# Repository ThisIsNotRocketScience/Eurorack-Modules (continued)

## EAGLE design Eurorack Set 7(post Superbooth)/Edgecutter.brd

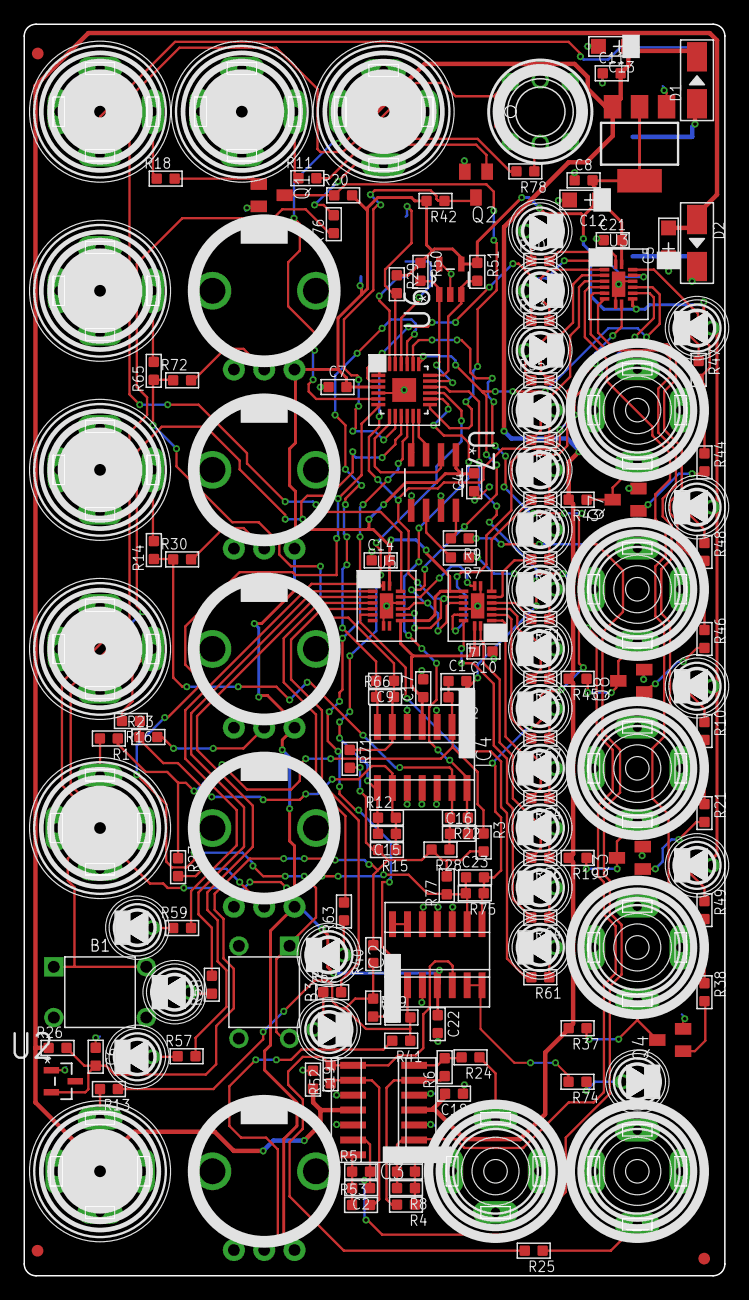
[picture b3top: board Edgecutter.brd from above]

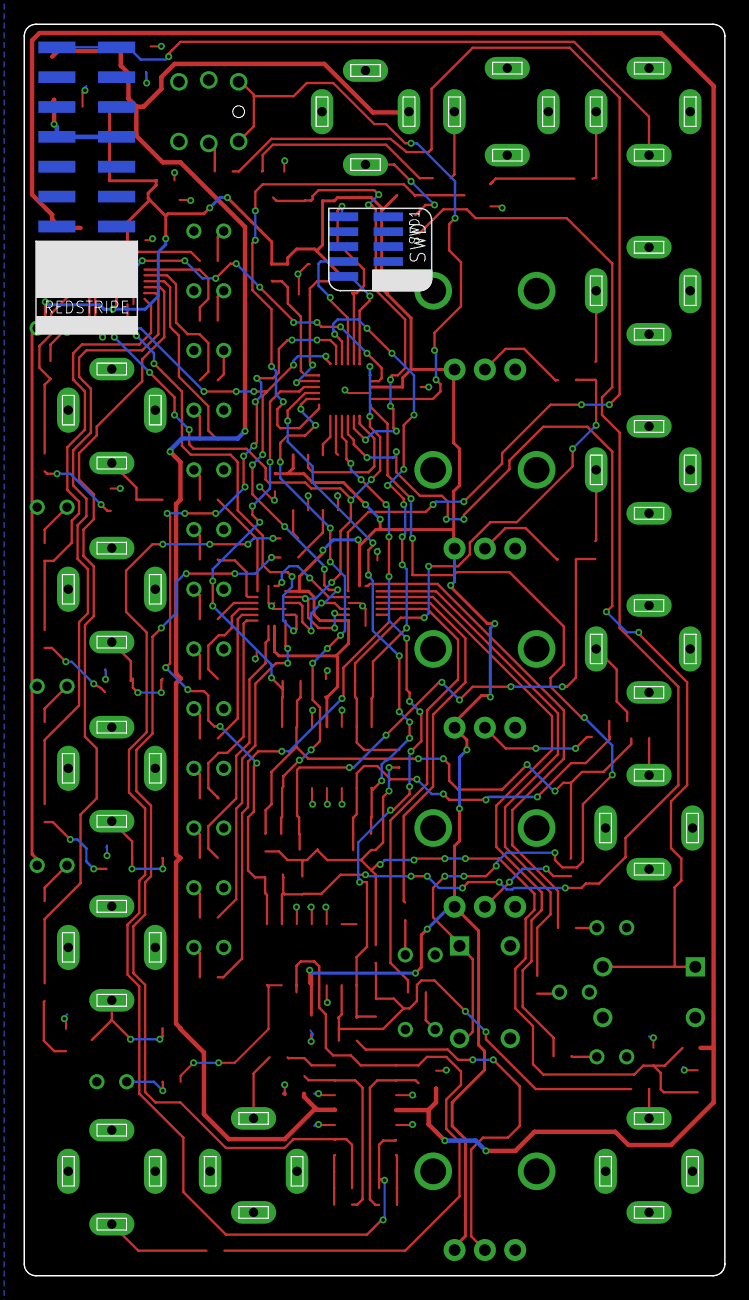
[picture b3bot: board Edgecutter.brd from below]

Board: 2 copper layers, 59.6 x 106.5 mm, 166 parts (2 on the bottom side), 122 nets.

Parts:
B1, B3: BUTTON-4P-3110040P1; 4P-6.0X6.0X5.0H
C1, C2, C3, C9, C15, C16, C20, C23: 3.3nF; C0603
C4, C6, C7, C8, C10, C11, C14, C17, C18, C19, C21, C22: 100nF; C0603
C5, C12, C13: 10uF; AVX-A
D1, D2: MRA4004T3G; DO-214AC
D3, D4, D5, D24, D25, D26, D27, D28, D29, D30, D31, D32, D33, D34, D35, D36, D37, D38, D39, D40, D41, D43, D44: yellow; 3MMLED
FID1, FID2, FID3: FIDUCIAL; FIDUCIAL_1MM
IC1: LD1117AS33TR; SOT223
IC2, IC4: MCP6004; SO14
IC3: TL074D; SO14
J1, J2, J3, J4, J5, J6, J9, J15: PJ-341; 3.5MM-JACK-SWITCH-13MM-INPUT
J7, J8, J10, J11, J12, J13: PJ-341; 3.5MM-JACK-SWITCH-13MM-OUTPUT
J14: POWERSMT; 2X08_SMT_HEADER
OUTLINE: EURORACK_PCB12HP; EURORACK12HPPCB
Q1, Q2, Q3, Q4, Q7, Q8: MMBT3904; SOT23-BEC
R1, R4, R6, R11, R13, R14, R16, R18, R21, R38, R44, R46, R52, R53, R65, R76: 100k; R0603
R2, R12, R22, R23, R27, R30, R39, R41, R66, R72, R75: 33k; R0603
R3, R15, R28, R40, R71, R77: 51k; R0603
R5, R8: 30k; R0603
R7, R9: 12k; R0603
R10, R31, R32, R33, R34, R35, R36, R47, R48, R49, R54, R55, R56, R57, R58, R59, R60, R61, R62, R63, R64, R67, R74, R78: 56; R0603
R17, R68, R69, R70, R73: 10kB; OG-POTS_ALPS_POT_VERTICAL
R19, R20, R26, R29, R37, R42, R43, R45: 10k; R0603
R24, R25: 100; R0603
R50, R51: 2k; R0603
SWD1: CORTEX_SWD; M50-3600542
U1: MKL02Z32VFK4; QFN50P400X400X100-25N
U2: LM4040DIM3-5.0; SOT95P237X112-3N
U3, U4, U5: 74HC595BQ; QFN50P250X350X100-17N
U6: 24LC16T-I/OT; SOT95P290X145-5N
U7: MCP4822-E/SN; SOIC8-N_MC
U$2: SWITCH_W_LED_PB6149L-X-102YELLOW; PB6149L

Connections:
3.3V: C4.2, C7.2, C8.2, C10.2, C12.+, C14.2, C17.1, C21.2, C22.1, D40.+, D41.+, D43.+, D44.+, IC1.2, IC1.4, IC2.4, IC4.4, R17.P$3, R20.2, R29.1, R42.2, R50.1, R51.1, R68.P$3, R69.P$3, R70.P$3, R73.P$3, SWD1.1, U1.3, U3.10, U3.16, U4.10, U4.16, U5.10, U5.16, U6.4, U7.1
12V: C11.2, C13.+, C18.2, D1.2, IC1.3, IC3.4, J9.SWITCH@3, R19.2, R37.2, R43.2, R45.2
-12V: C5.-, C19.2, D2.1, IC3.11, R26.1
ADC_ATTACK: C9.2, IC4.7, R66.1, U1.21
ADC_CURVE: C20.2, IC2.1, R39.1, U1.10
ADC_DECAY: C16.2, IC4.14, R22.1, U1.14
ADC_RELEASE: C1.2, IC4.1, R2.1, U1.16
ADC_SUSTAIN: C15.2, IC4.8, R12.1, U1.15
ADC_VELOCITY: C23.2, IC2.8, R75.1, U1.20
BUTTON_LOOP: B3.1, B3.4, U1.6
BUTTON_TIMERANGE: B1.1, B1.4, U1.9
BUTTON_TRIGGER: U1.5, U$2.1, U$2.2
CLOCK: U1.1, U3.11, U4.11, U5.11
CPU_RESET: R29.2, SWD1.10, U1.23
D21: D43.-, R47.1
DACCS: U1.7, U7.2
DACSCK: U1.12, U7.3
DACSDI: U1.11, U7.4
EXTGATE: J5.SWITCH@3, J14.15, J14.16
GND: B1.2, B1.3, B3.2, B3.3, C4.1, C5.+, C6.1, C7.1, C8.1, C10.1, C11.1, C12.-, C13.-, C14.1, C17.2, C18.1, C19.1, C21.1, C22.2, D3.-, D4.-, D5.-, D24.-, D25.-, D26.-, D27.-, D28.-, D29.-, D30.-, D31.-, D32.-, D33.-, D34.-, D35.-, D36.-, D37.-, D38.-, D39.-, IC1.1, IC2.3, IC2.10, IC2.11, IC2.12, IC3.3, IC3.5, IC3.10, IC3.12, IC4.3, IC4.5, IC4.10, IC4.11, IC4.12, J1.RING@3, J1.SWITCH@3, J2.RING@3, J2.SWITCH@3, J3.RING@3, J3.SWITCH@3, J4.RING@3, J4.SWITCH@3, J5.RING@3, J6.RING@3, J6.SWITCH@3, J7.RING@3, J8.RING@3, J9.RING@3, J10.RING@3, J11.RING@3, J12.RING@3, J13.RING@3, J14.3, J14.4, J14.5, J14.6, J14.7, J14.8, J15.RING@3, J15.SWITCH@3, Q1.E, Q2.E, Q3.E, Q4.E, Q7.E, Q8.E, R17.P$1, R68.P$1, R69.P$1, R70.P$1, R73.P$1, SWD1.3, SWD1.5, U1.4, U1.25, U2.1, U3.8, U3.13, U3.17, U4.8, U4.13, U4.17, U5.8, U5.13, U5.17, U6.2, U6.5, U7.5, U7.7, U$2.3, U$2.4, U$2.LEDNEG
KNOB_ATTACK: R72.2, R73.P$2
KNOB_CURVE: R41.2, R70.P$2
KNOB_DECAY: R17.P$2, R30.2
KNOB_RELEASE: R27.2, R69.P$2
KNOB_SUSTAIN: R23.2, R68.P$2
LATCH: U1.19, U3.12, U4.12, U5.12
unnamed: R78.1, U$2.LEDPOS
unnamed: IC3.6, R4.2, R6.1
unnamed: J2.TIP@3, R16.2
unnamed: C15.1, IC4.9, R12.2, R15.1, R16.1, R23.1
unnamed: R9.2, U7.8
unnamed: J3.TIP@3, R1.2
unnamed: R7.2, U7.6
unnamed: C1.1, IC4.2, R1.1, R2.2, R3.1, R27.1
unnamed: C2.1, IC3.13, R5.2, R9.1
unnamed: C3.1, IC3.2, R7.1, R8.2
unnamed: J15.TIP@3, R65.2
unnamed: J4.TIP@3, R13.2
unnamed: D1.1, J14.9, J14.10
unnamed: R34.2, U4.7
unnamed: Q1.B, R18.2
unnamed: J5.TIP@3, R18.1
unnamed: IC3.9, R52.1, R53.2
unnamed: C3.2, IC3.1, R4.1, R8.1
unnamed: IC2.6, IC2.7, R74.2
unnamed: J13.TIP@3, R25.1
unnamed: J12.TIP@3, R24.1
unnamed: C9.1, IC4.6, R65.1, R66.2, R71.1, R72.1
unnamed: D40.-, R10.1
unnamed: C2.2, IC3.14, R5.1, R53.1
unnamed: Q3.B, R21.2
unnamed: IC2.13, IC2.14
unnamed: R64.2, U4.15
unnamed: D28.+, R62.1
unnamed: J7.TIP@3, Q3.C, R19.1
unnamed: D4.+, R67.1
unnamed: R60.2, U3.1
unnamed: D29.+, R61.1
unnamed: J1.TIP@3, R14.2
unnamed: C16.1, IC4.13, R14.1, R22.2, R28.1, R30.1
unnamed: R33.2, U3.2
unnamed: R55.2, U3.3
unnamed: R35.2, U3.4
unnamed: R56.2, U4.1
unnamed: R54.2, U4.2
unnamed: R67.2, U4.3
unnamed: R32.2, U4.4
unnamed: R31.2, U4.5
unnamed: Q2.B, R11.2
unnamed: D41.-, R49.1
unnamed: D44.-, R48.1
unnamed: C20.1, IC2.2, R13.1, R39.2, R40.1, R41.1
unnamed: J6.TIP@3, R11.1
unnamed: R36.2, U4.6
unnamed: R59.2, U5.1
unnamed: R58.2, U5.2
unnamed: D3.+, R60.1
unnamed: R57.2, U5.3
unnamed: R63.2, U5.4
unnamed: R62.2, U5.5
unnamed: R61.2, U5.6
unnamed: C23.1, IC2.9, R75.2, R76.1, R77.1
unnamed: Q4.B, R38.2
unnamed: J8.TIP@3, Q4.C, R37.1
unnamed: D5.+, R74.1
unnamed: J9.TIP@3, R76.2
unnamed: D2.2, J14.1, J14.2
unnamed: Q7.B, R44.2
unnamed: J10.TIP@3, Q7.C, R43.1
unnamed: Q8.B, R46.2
unnamed: J11.TIP@3, Q8.C, R45.1
unnamed: D27.+, R57.1
unnamed: D26.+, R56.1
unnamed: D25.+, R58.1
unnamed: D24.+, R59.1
unnamed: D30.+, R63.1
unnamed: D31.+, R64.1
unnamed: D32.+, R33.1
unnamed: D33.+, R32.1
unnamed: D34.+, R31.1
unnamed: D35.+, R34.1
unnamed: D36.+, R55.1
unnamed: D37.+, R54.1
unnamed: D38.+, R35.1
unnamed: D39.+, R36.1
OUT_ATTACK: R44.1, R47.2, U3.15
OUT_CUR_PRERES: IC2.5, IC3.8, R25.2, R52.2
OUT_DECAY: R46.1, R48.2, U3.7
OUT_LIN_PRERES: IC3.7, R6.2, R24.2
OUT_RELEASEDONE: R38.1, R49.2, U3.5
OUT_RELEASESTART: R10.2, R21.1, U3.6
REF_-5V: C6.2, R3.2, R15.2, R26.2, R28.2, R40.2, R71.2, R77.2, U2.2
RETRIGGER_ENVELOPE: Q2.C, R42.1, U1.8
SCL: R50.2, U1.17, U6.1
SDA: R51.2, U1.18, U6.3
SHIFTER1TO2: U3.9, U4.14
SHIFTER2TO3: U4.9, U5.14
SHIFTERS: U1.2, U3.14
SWD_CLK: SWD1.4, U1.22
SWD_DIO: SWD1.2, U1.24
TRIGGER_ENVELOPE: Q1.C, R20.1, U1.13
TRIGGER_LED: R78.2, U5.15

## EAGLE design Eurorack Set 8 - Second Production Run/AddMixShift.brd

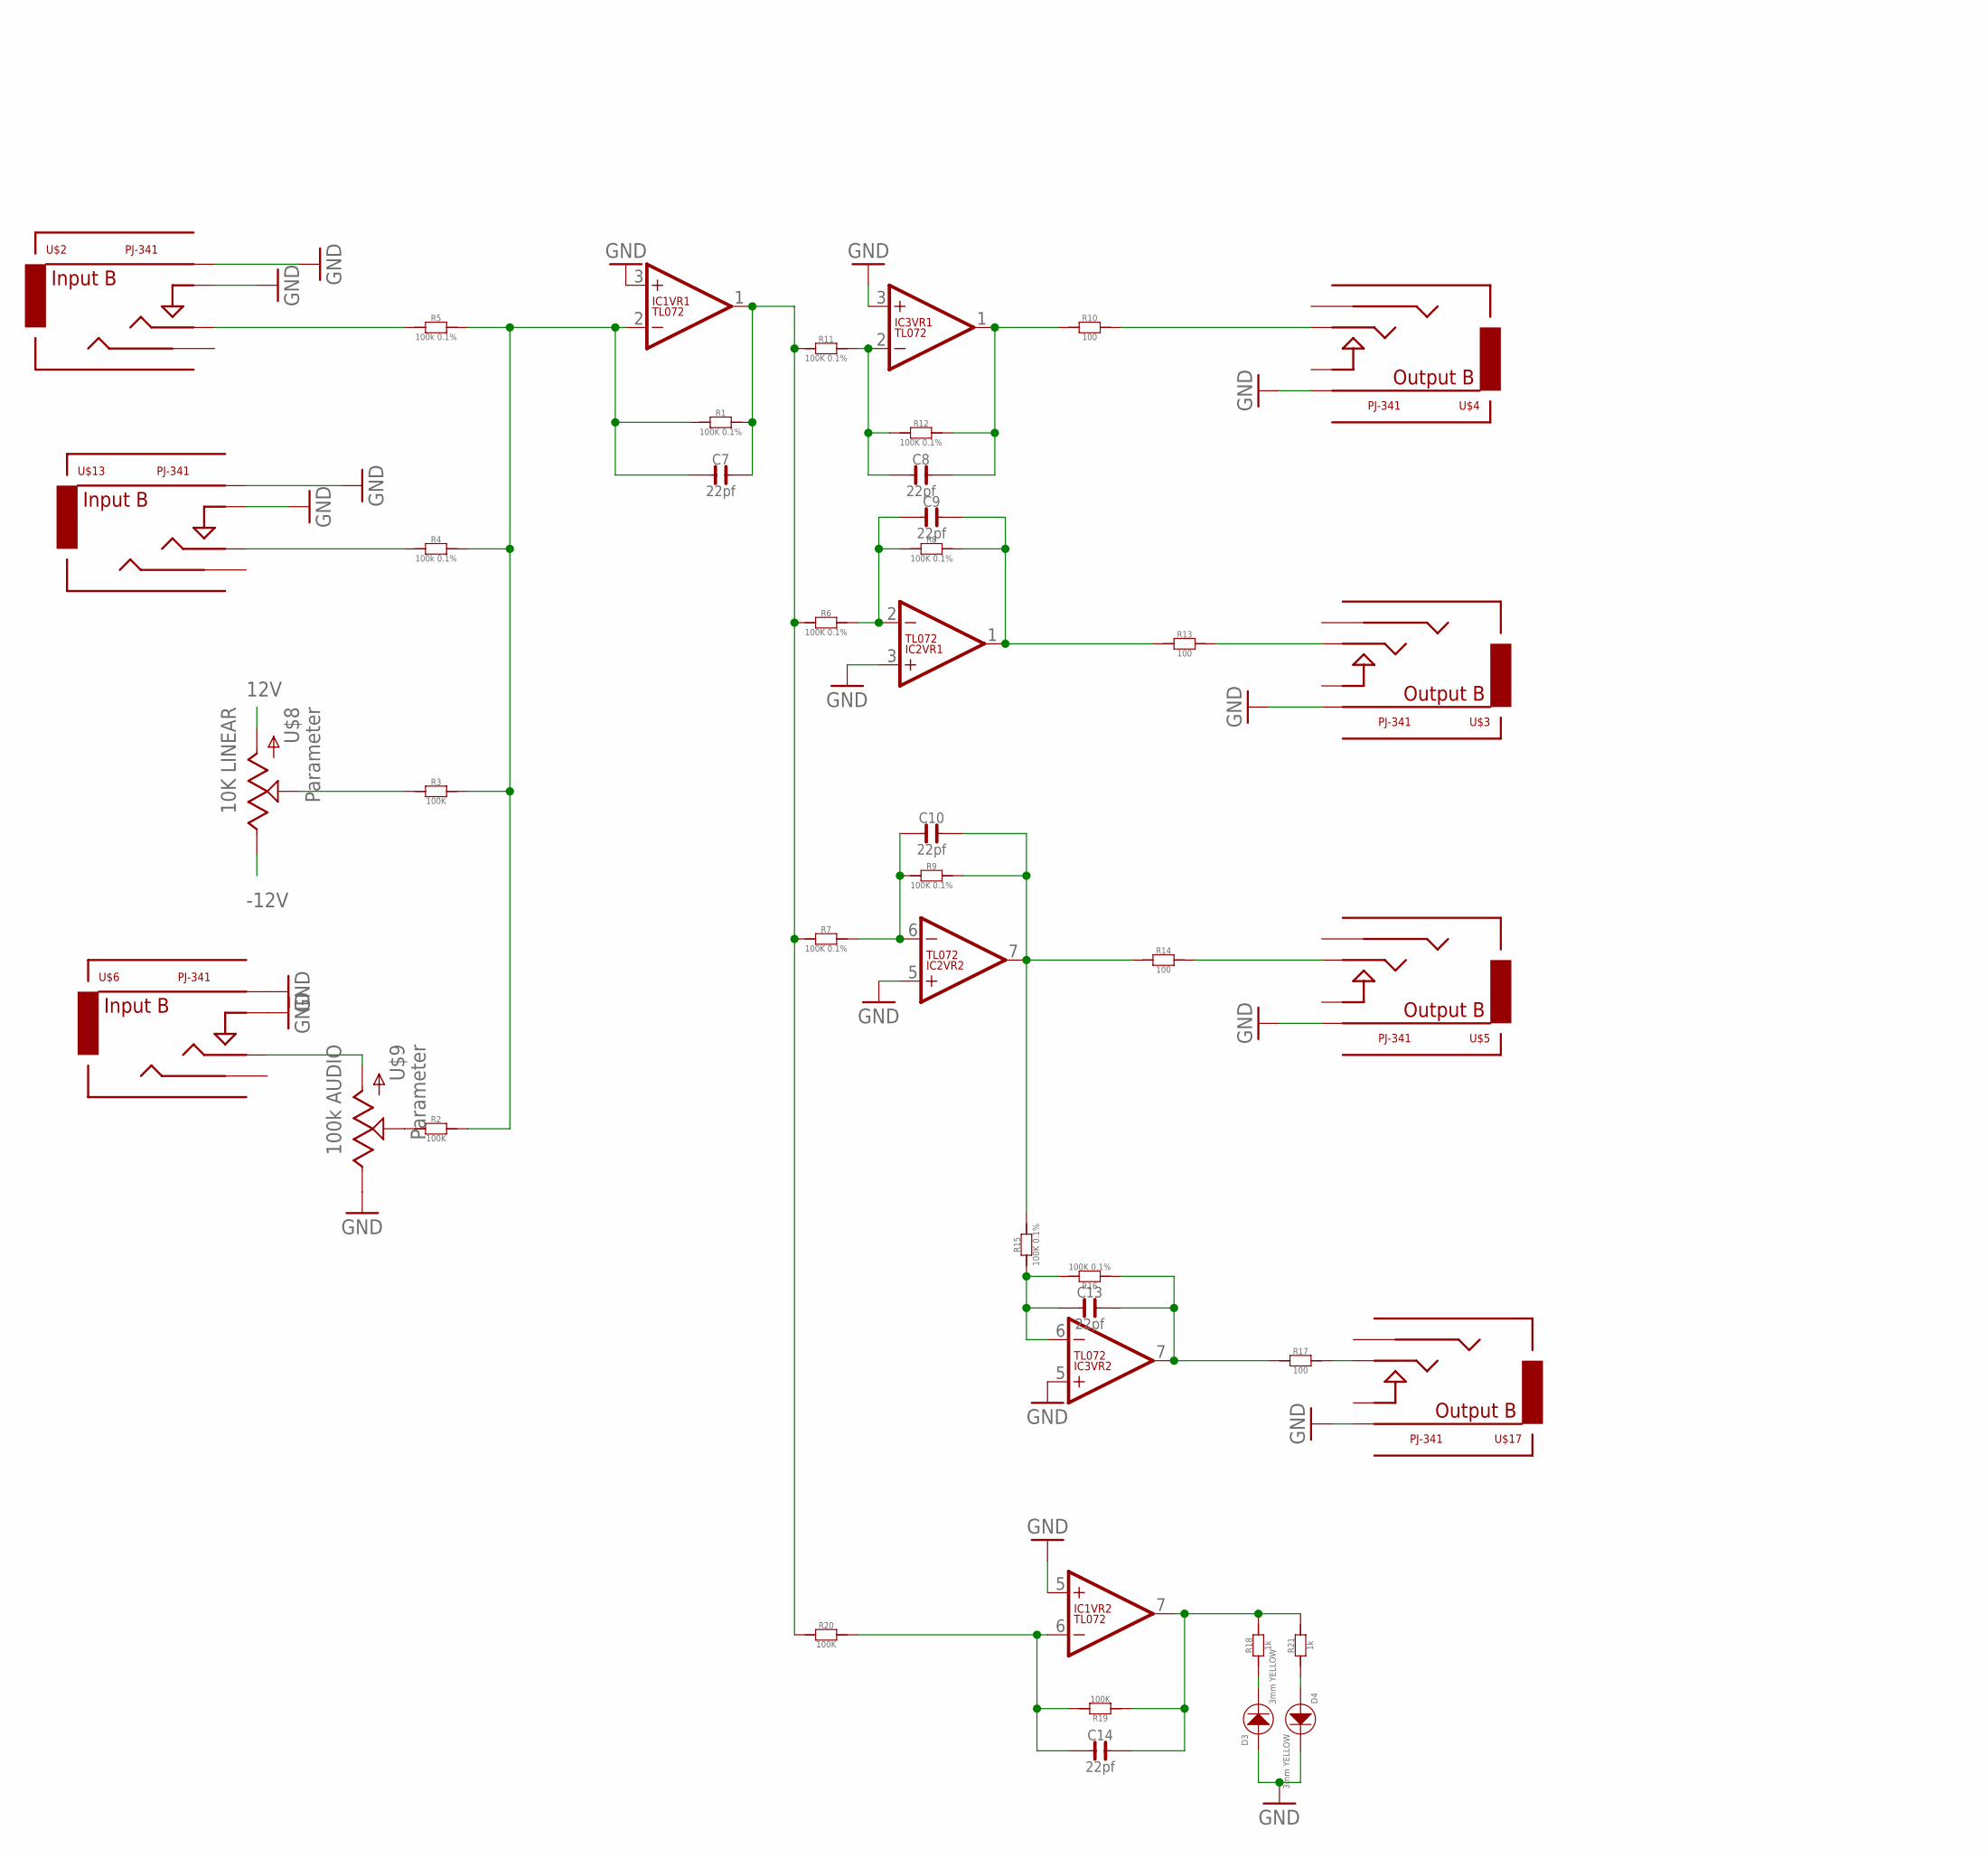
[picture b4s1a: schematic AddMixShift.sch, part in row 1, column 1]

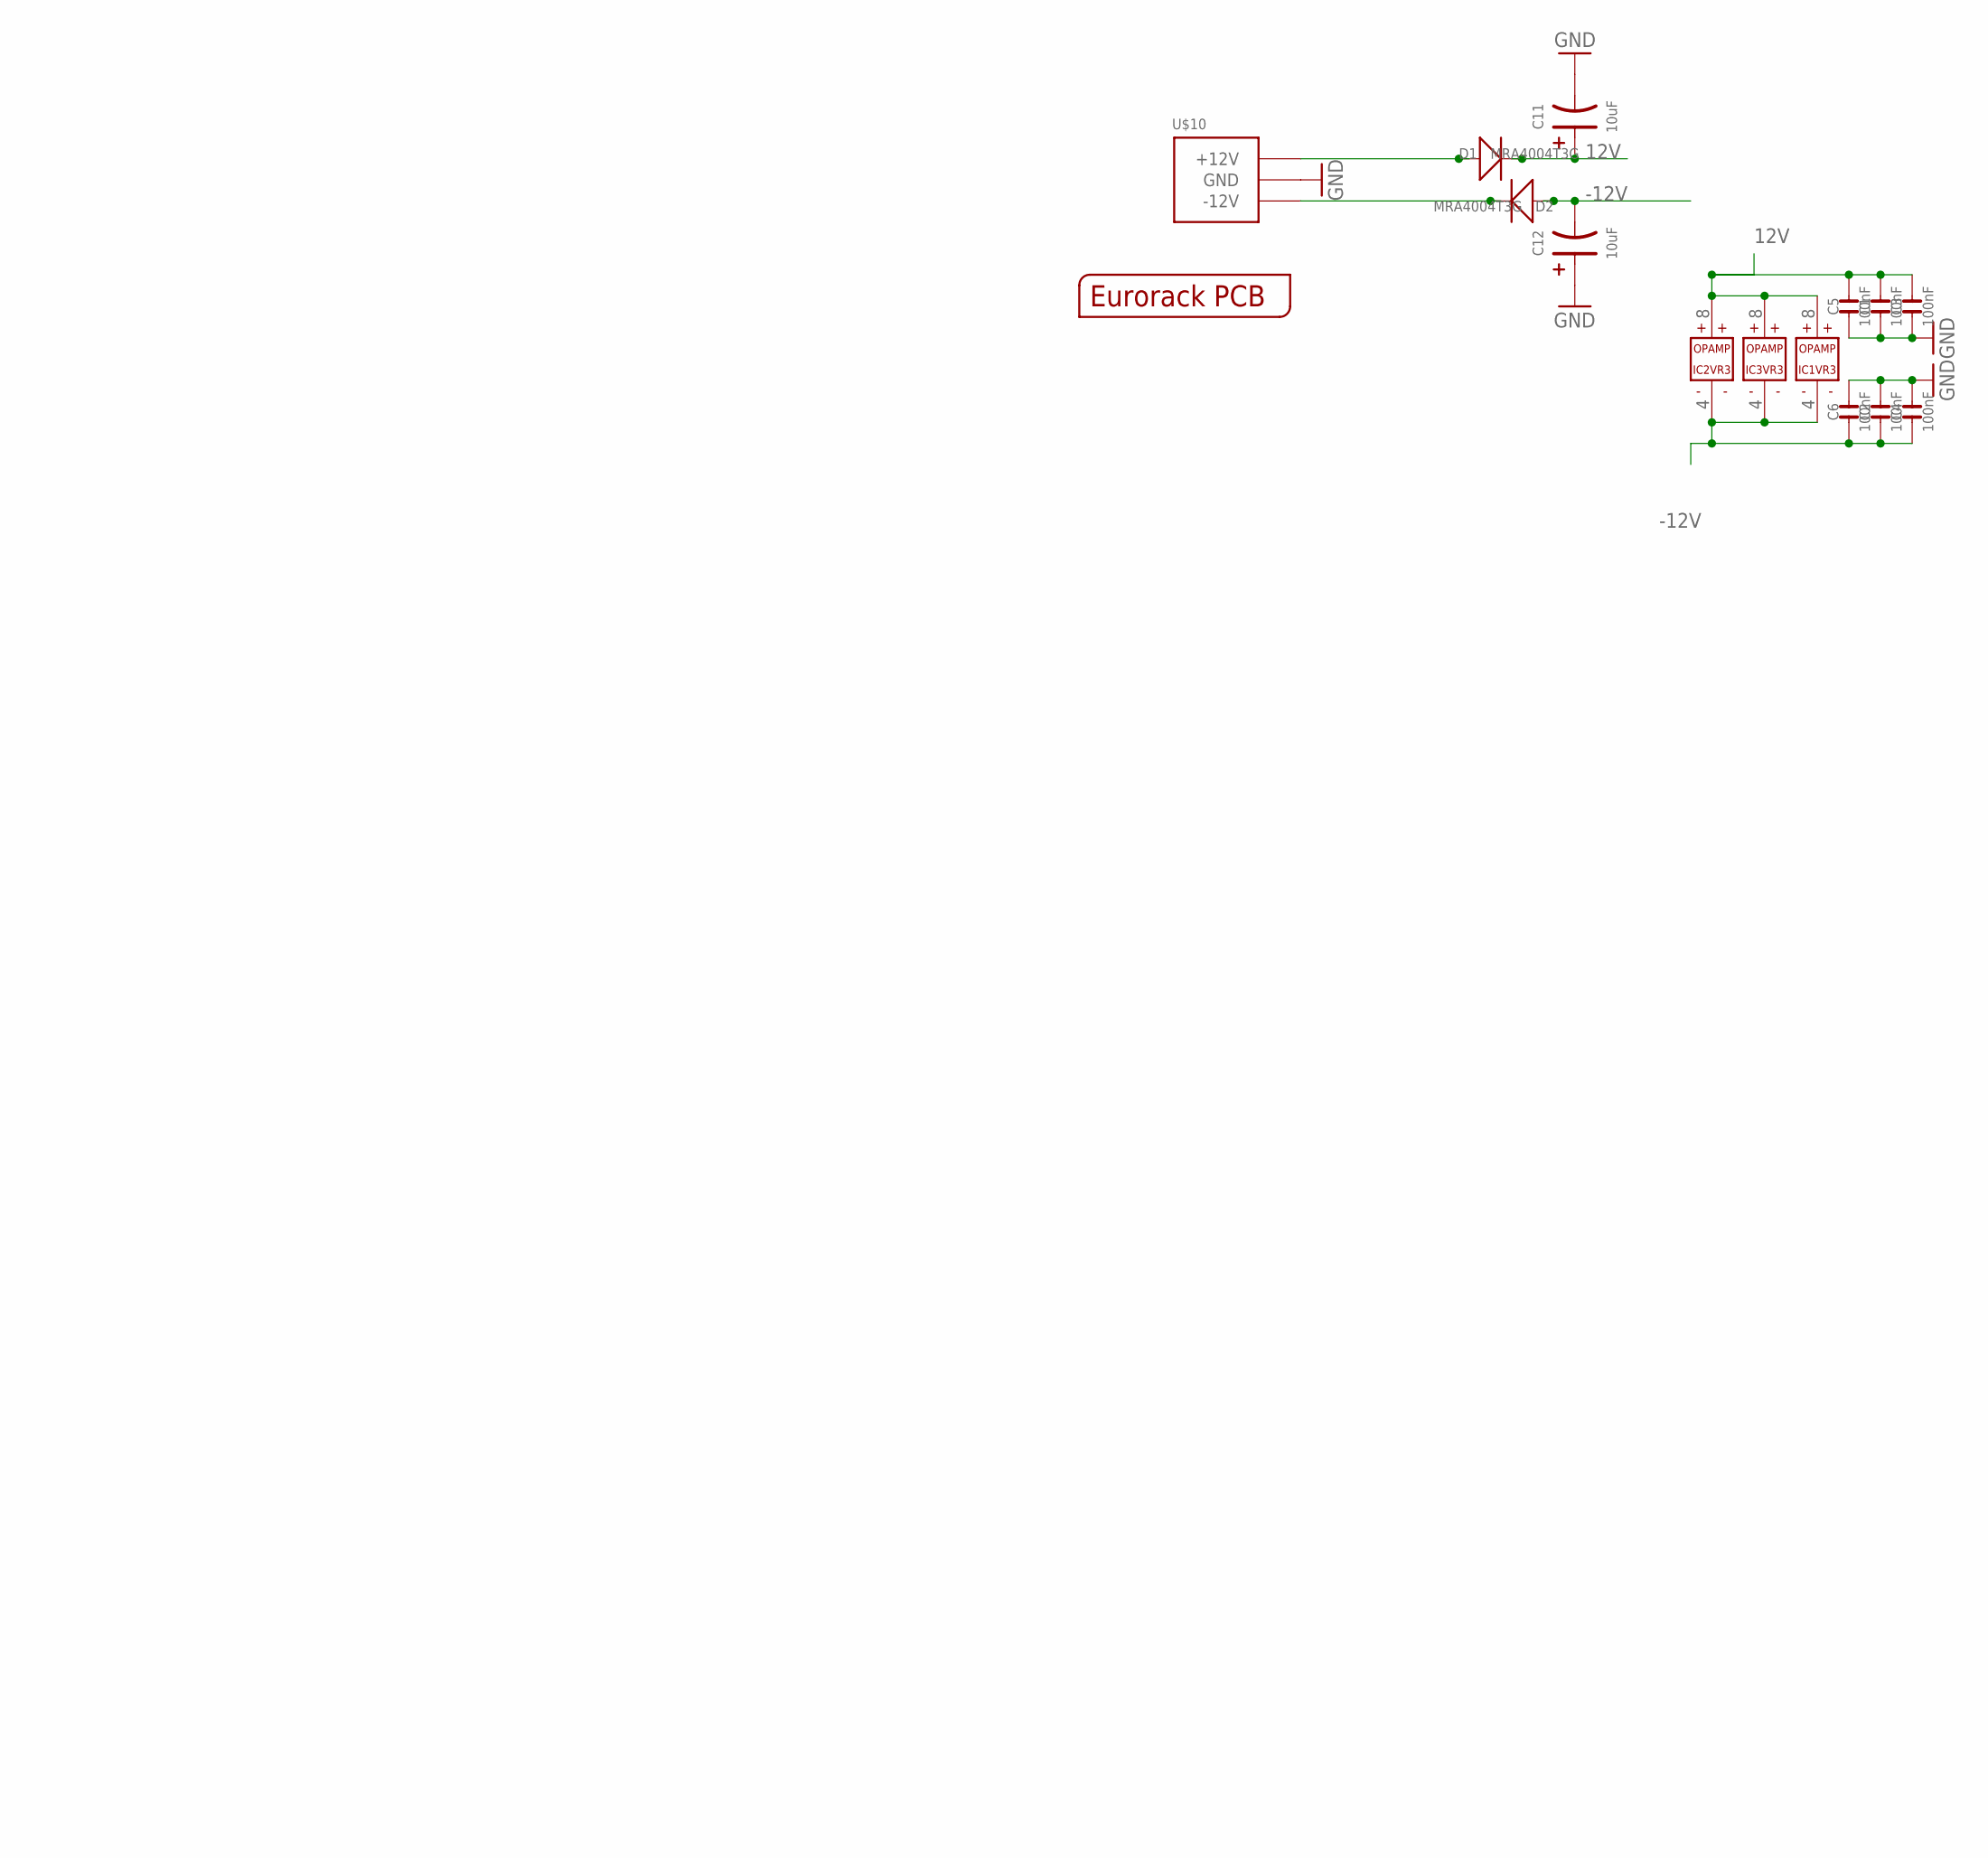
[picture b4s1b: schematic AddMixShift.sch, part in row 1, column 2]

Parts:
C1, C2, C3, C4, C5, C6: 100nF; C0603
C7, C8, C9, C10, C13, C14: 22pf; C0603
C11, C12: 10uF; AVX-A
D1, D2: MRA4004T3G; DO-214AC; MPN US1G-E3/5AT
D3, D4: 3mm YELLOW; 3MMLED
IC1, IC2, IC3: TL072; SO08
R1, R6, R7, R8, R9, R11, R12, R15, R16: 100K 0.1%; R0603
R2, R3, R19, R20: 100K; R0603
R4, R5: 100k 0.1%; R0603
R10, R13, R14, R17: 100; R0603
R18, R21: 1k; R0603
U$1: EURORACK_PCB4HP; EURORACK4HPPCB
U$2, U$6, U$13: PJ-341; 3.5MM-JACK-SWITCH-13MM-INPUT
U$3, U$4, U$5, U$17: PJ-341; 3.5MM-JACK-SWITCH-13MM-OUTPUT
U$8: 10K LINEAR; OG-POTS_ALPS_POT_VERTICAL
U$9: 100k AUDIO; OG-POTS_ALPS_POT_VERTICAL
U$10: POWER_SIMPLE; 2X05_SMT_HEADER

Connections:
12V: C1.2, C3.2, C5.2, C11.+ (1), D1.2 (-), IC1.8 (V+), IC2.8 (V+), IC3.8 (V+), U$8.P$3 (A)
-12V: C2.1, C4.1, C6.1, C12.- (2), D2.1 (+), IC1.4 (V-), IC2.4 (V-), IC3.4 (V-), U$8.P$1 (E)
GND: C1.1, C2.2, C3.1, C4.2, C5.1, C6.2, C11.- (2), C12.+ (1), D3.+, D4.-, IC1.3 (+IN), IC1.5 (+IN), IC2.3 (+IN), IC2.5 (+IN), IC3.3 (+IN), IC3.5 (+IN), U$2.RING@3 (RING), U$2.SWITCH@3 (SWITCH), U$3.RING@3 (RING), U$4.RING@3 (RING), U$5.RING@3 (RING), U$6.RING@3 (RING), U$6.SWITCH@3 (SWITCH), U$9.P$1 (E), U$10.3 (GND), U$10.4 (GND), U$10.5 (GND), U$10.6 (GND), U$10.7 (GND), U$10.8 (GND), U$13.RING@3 (RING), U$13.SWITCH@3 (SWITCH), U$17.RING@3 (RING)
unnamed: R2.1, U$9.P$2 (S)
unnamed: C8.2, IC3.1 (OUT), R10.1, R12.2
unnamed: U$6.TIP@3 (TIP), U$9.P$3 (A)
unnamed: C9.1, IC2.2 (-IN), R6.2, R8.1
unnamed: R3.1, U$8.P$2 (S)
unnamed: C7.2, IC1.1 (OUT), R1.2, R6.1, R7.1, R11.1, R20.1
unnamed: C8.1, IC3.2 (-IN), R11.2, R12.1
unnamed: C10.1, IC2.6 (-IN), R7.2, R9.1
unnamed: C9.2, IC2.1 (OUT), R8.2, R13.1
unnamed: R4.1, U$13.TIP@3 (TIP)
unnamed: C10.2, IC2.7 (OUT), R9.2, R14.1, R15.2
unnamed: C7.1, IC1.2 (-IN), R1.1, R2.2, R3.2, R4.2, R5.2
unnamed: R13.2, U$3.TIP@3 (TIP)
unnamed: R14.2, U$5.TIP@3 (TIP)
unnamed: C13.1, IC3.6 (-IN), R15.1, R16.2
unnamed: C13.2, IC3.7 (OUT), R16.1, R17.1
unnamed: R17.2, U$17.TIP@3 (TIP)
unnamed: R5.1, U$2.TIP@3 (TIP)
unnamed: D4.+, R21.1
unnamed: R10.2, U$4.TIP@3 (TIP)
unnamed: D3.-, R18.1
unnamed: C14.2, IC1.7 (OUT), R18.2, R19.1, R21.2
unnamed: C14.1, IC1.6 (-IN), R19.2, R20.2
unnamed: D1.1 (+), U$10.9 (+12V), U$10.10 (+12V)
unnamed: D2.2 (-), U$10.1 (-12V), U$10.2 (-12V)

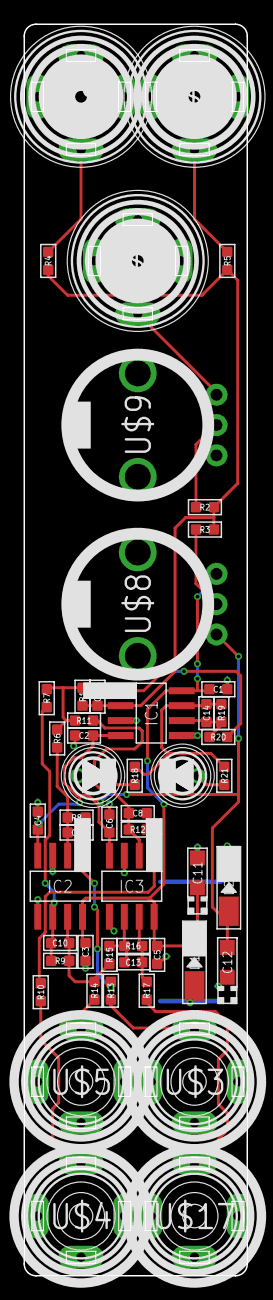
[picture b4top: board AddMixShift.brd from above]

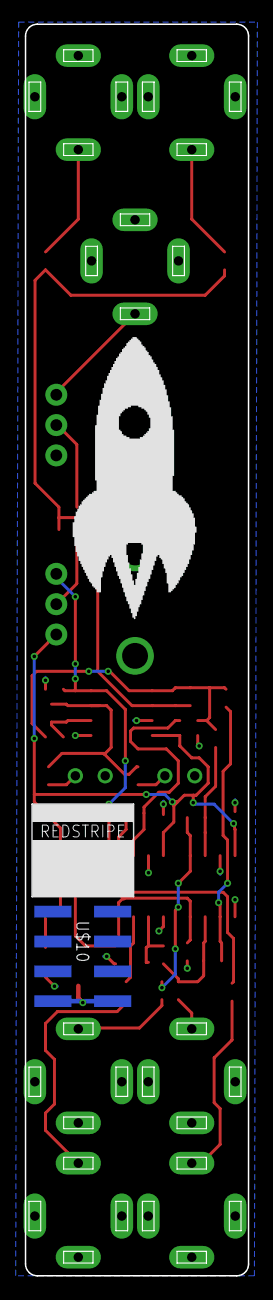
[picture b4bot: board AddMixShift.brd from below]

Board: 2 copper layers, 19.0 x 106.5 mm, 54 parts (2 on the bottom side), 28 nets.

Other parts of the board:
U$11: TINRS_ARTWORKROCKET; TINRS_ROCKET
